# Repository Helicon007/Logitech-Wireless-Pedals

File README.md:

# Logitech G27 Wireless Pedals per ESP-NOW
Ich fahre nur gelegentlich ein paar Runden GT7 und hab dazu noch ein altes Logitech G27 Lenkrad mit Pedalen. Ich musste bereits den optischen Encoder reparieren und war vertraut damit das Lenkrad zu zerlegen. Um das G27 an einer PS5 lauffähig zu bekommen ist ein Adapter nötig, ich nutze den [Ras1ution 2](https://www.brookaccessory.com/products/ras1ution2/index.html) und bin soweit zufrieden, allerdings ist der mittlerweile so teuer dass man auch über ein neues kompatibles Lenkrad nachdenken könnte. 
Da ich mein Setup regelmäßig am Schreibtisch auf- und abbaue habe ich das optimiert. Lenkrad und Schalthebel sind auf einem laminierten Brett geschraubt und die Pedale haben Schienen mit denen ich den Abstand zum Bürostuhl fixieren kann. Das hat aber leider zu Folge dass die Leitungen am Lenkrad fest verbunden sind und beim aufräumen das Kabel zu den Pedalen sehr stört. Das Brett mit Lenkrad und Schalthebel ist quasi über das dünne Kabel mit den Pedalen fest verbunden. Warum also das ganze nicht schnurlos gestalten, die Elektronik hierfür habe ich daheim und ich war eh auf der Suche nach einem neuen Projekt? 
Das ist ein Blog oder Erfahrungsbericht, keine Anleitung. Grundkenntnisse in Elektronik und ESP sind vorausgesetzt. Gerne beantworte ich Fragen aber ich erhebe hier keinen Anspruch auf ein Projekt was problemlos nachgebaut werden kann.

Die Kernelemente sind zwei ESP8622 Boards in Form eines ESP-01 und eines Wemos Klons. Stromversorgung beim Empfänger sollte im Lenkrad zu finden sein, für die Pedale brauchen wir eine Akku-Schaltung mit Ladeelektronik die lange genug durchhält. Eine 18650 Lithium Zelle ist üppig genug und sollte mit 2000mAh circa 11-12h durchhalten. Der Sender benötigt circa 120-150mA, aber zur Wahrheit gehört auch dass wir nicht die gesamte Kappazität der Batterie nutzen können weil unter 3V der ESP dann irgendwann aussteigt. Der Spannungsregler hat entsprechend auch einen Spannungsabfall von 0.1-0.2V. Ich habe mich an fertigen Breakout Boards bedient die ich dann auf einer Lochrasterplatine mit Kupferlackdrähten verbunden habe. Natürlich wäre das alles auf einer schicken Platine schöner aber ich hatte nicht geplant hiermit in die Serienfertigung zu. gehen, das Projekt ist für mich und ich Teile nur meine Erfahrungen falls jemand etwas ähnliches vor hat. 
Die Stücklliste der fertigen Boards:
* ESP-01 + Programmieradapter
* Spannungsregler 3.3V
* Ladeschaltung Li-Ion Akku
* USB-PD Board (optional)
* ADS1115 4-Kanal AD-Wandler mit I2C Bus
* Wemos Pro mini
* Levelshifter 3.3V <—> 5V
* I2C Display (optional)
* Lochrasterplatine
* Kupferlackdraht
* Steckverbinder (Set mit Crimpzange)
* 18650 Akkuzelle mit Halter
* Ein/Aus-Schalter

# Der Sender
Das USB-C PD-Board habe ich genommen weil damit sicher gestellt ist dass auch ein PD-Netzteil Spannung liefert und auch der maximale Ladestrom von 1A damit erreicht werden kann. Ohne dieses funktioniert die Ladeschaltung natürlich auch. Ich hatte aber nur Boards mit Micro-USB Buchse und ein PD-Netzteil würde auch keine Spannung liefern. Ein  USB-A Kabel auf Micro-USB würde funktionieren aber das wollte ich nicht. Ich bin froh wenn irgendwann alle meine Geräte nur noch USB-C benutzen. Deshalb der Aufwand mit dem PD-Breakout Board um mit den 5V dann direkt in das Ladeboard zu gehen. Ich habe hier eins mit Schutzschaltung genommen das vor Unterspannung und Kurzschlussstrom schützt.  Der Ausgang des Boards wird mit dem Spannungswandler verbunden an dem dann der ESP-01 und der ADS1115 angeschlossen wird. Der ESP-01 hat keinen AD Wandler und wir würden ja auch mindestens 3 benötigen, das bietet auch kein Wemos. Weiter ist der on-Board AD Wandler sehr ungenau und von der Versorgungsspannung abhängig. Das AD1115 Board liefert uns hingegen 4 AD-Wander mit eigener Referenzspannung, mit 16 Bit Auflösung und hoher Samplingrate von maximal 860 sps (bei 4 Kanälen entsprechend 860/4). Da bleibt auch noch ein Kanal frei um die Akkuspannung zu überwachen, das ist optional. Genauso wie das OLED Display am Empfänger kann man das auch einfach weglassen. 

Unter dem ADS1115 befindet sich ein einfach Spannungteiler für die Batteriespannung. Die gemessene Spannung darf nicht über den 3,3V VDD liegen und der Akku kann ja bis zu 4,2V haben. Deshalb kommt hier eine Reihenschaltung von 220kOhm und 100kOhm als Teiler.

Ubat —|100k|— A0 — |220k| — GND

Den ADS1115 habe ich ohne Stecksockel auf der Platine verlötet damit ich die Boards stapeln kann und die Fläche klein bleibt. 

Die Pedale bestehen aus je einem 10kOhm Poti. Vom Lenkrad kommen 5V und GND und entsprechend wird an jedem Pedal die Signalspannung abgegriffen. Das ganze funktioniert natürlich auch mit 3,3V da wir ja nur die Position benötigen von 0-100% und einen Rohwert des AD Wandlers verschicken. Auf der Empfängerseite versuchen wir dann wieder so gut wie möglich 0-5V daraus zu machen. 
Den Ein-/Ausschalter habe ich direkt mit der Batteriemasse verbunden. Nicht ganz optimal weil dadurch auch nur im eingeschalteten Zustand der Akku geladen werden kann. Besser wäre es gewesen den Schalter in die Verbindung zur Hauptplatine zu bauen. Andererseits ist das dank Power Delivery Schaltung auch kein Problem zu den 1A Ladestrom auch die 150mA für die Schaltung zu bekommen. Deshalb habe ich es letztlich so gelassen. 
Die vorhandenen Kabel zum Lenkrad habe ich weitergenutzt. Den langen Teil abgeschnitten und einen Stecker für die Hauptplatine angeschlossen. Das war es dann auch auf Senderseite. Natürlich muss auf dem ESP-01 die Sendersoftware auch installiert werden. Wie das funktioniert setze ich voraus, hierfür gibt es aber auch genügend Anleitungen im Netz weshalb ich darauf nicht eingehe. Nur die MAC Adresse des Empfängers ist hart im Programmcode festgelegt und muss entsprechend angepasst werden. Man könnte natürlich auch Broadcast an alle ESP senden aber die Reichweite ist doch recht hoch und ich hab mich für die 1:1 Verbindung entschieden. 

Für die Lade-LEDs habe ich noch zwei 1,5mm Löcher ins Gehäuse gebohrt und anschliesend die Platine danach ausgerichtet und mit Heißkleber fixiert. 
Auch die Kabel sind mit Heißkleber fixiert und einige Stege aus dem Gehäusedeckel eingeschnitten um zu verhindern dass Kabel gequetscht werden. Beim Verschrauben kann man sonst leicht einige Kabel noch beschädigen. 

# Der Empfänger
Ein Wemos Klon gepaart mit einem Level Shifter schien mir hier die einfachste Wahl. Ganz so einfach war es dann aber doch leider nicht. Da ich davon augegangen bin dass der Prozessor im Lenkrad ein glattes Analogsignal sehen möchte und nicht die PWM Ausgänge eines ESP musste die Spannung nachträglich geglättet werden. Die bekannten Levelshifter sind aber sehr hochohmig (10kOhm) was ein RC Tiefpass einfach zu träge gemacht hat. Ich erreichte so aus dem PWM Signal mit 3,3V leider keine 5V. Tatsächlich gehen die 0-100% der Pedale in einer Spannung von 0,6V-4,6V aus, das hab ich im originalzustand vorher gemesssen. Aber auch von den 4,6V war ich noch weit weg. Ein funktionierender Tiefpass würde aus einem 1kOhm Widerstand in Reihe und 10µF Kapazität nach Masse bestehen. So ein Level Shifter hat aber von HV zum Ausgang einen 10kOhm Widerstand. 

Um ausreichend Ladestrom für den 10µF Kondensator am 5V Ausgang zu erhalten habe ich parallel zu R4 im Schaltbild einen 1000 Ohm Widerstand gelötet. Das kann man auf der Lochrasterplatine machen zwischen 5V und dem Ausgang. Somit fällt R4 knapp unter 1000 Ohm. Der Entladestrom des Elkos wäre aber viel zu hoch für den I/O des Wemos weshalb unbedingt zwischen dem Ausgang und dem Elko noch mal 1kOhm in Reihe geschaltet sein muss. Das begrenzt den Strom auf 5mA was für den Wemos kein Problem ist. Das RC Glied besteht dann am Ende aus 2kOhm und 10µF. Immer noch gut genug die Spannung zu glätten und ein Maximum von circa 4,6V zu erreichen. Damit ist dann auch der Prozessor im Lenkrad zufrieden.

Ich habe leider versäumt ein schönes Foto vom Levelshifter zu machen aber ich habe ihn direkt auf der Platine unter dem Wemos verlötet. Daneben sind die SMD Elkos zu erkennen und die Widerstände habe ich auf der Rückseite verlötet.

Das OLED ist komplett optional und hier nur gesteckt. Später im Lenkrad habe ich das über eine 4-adrige Leitung verbunden. Es zeigt mir später die Spannung der Senderbatterie an und den Zustand des Gas- und Bremspedals, allerdings nur mit Latenz. Das PWM Signal reagiert unmittelbar auf die Pedale aber das Display schreibe ich im Code nur einmal pro Sekunde. Ohne zu überprüfen dachte ich mir die Rechenzeit des ESP ist besser aufgehoben möglichst schnell das PWM anzupassen und weniger das Display. Die einzige sinnvolle Information ist die Batteriespannung und die muss nicht unmittelbar angezeigt werden. 

Der Anschluss der Pedale ist auf dem Mainboard unten links. Leider sind die Kabelfarben nicht identisch mit den Farben der Leitung zu den Pedalen. Gut wenn man sich vorher die Belegung vom Sub-D Stecker aufgeschrieben hat.

* 1 GND
* 2 Gas
* 3 Bremse
* 4 Kupplung
* 6 Enable Pin active high
* 9 +5V

Leider ist die Spannungsversorgung nicht ohne Schutzwiderstand und wir können die Schaltung nicht mit dem 5V Anschluss links betreiben. Die Spannung fällt augenblicklich auf 1V, ein Strom von 150mA kann hier nicht direkt abgegriffen werden. Deshalb habe ich die 5V direkt am USB Anschluss des Lenkrads abgegriffen, der grüne Pin am rechten Stecker. Hierfür brückte ich direkt auf der Rückseite mit einem Kupferlackdraht die Verbindung. Da auf den zwei Pins ohne Last dasselbe Potential lag machte ich mir über die Hauptplatine keine Sorgen. Vermutlich ist hier nur ein Schutzwiderstand eingebracht der die Platine vor einem Kurzschluss am Ausgang absichert der ja ohnehin nicht mehr benötigt wird. 

Der braune Pin ist wohl eine Art Enabler. Die Pedale werden erst erkannt wenn auf diesem Pin High anliegt, also mit 5V verbinden. USB Plus ist grün und das Kabel ist braun?! Verlasst Euch nicht auf irgendeine Farbenregel, messt selbst nach. Auf dem Sub-D Kabel ist Pin 9 und 6 verbunden. 
Jetzt noch einen Platz für die Platine und optional das Display finden und wir sind fertig.

Wie gesagt das Display ist komplett optional aber anders kann ich die Spannung des Akkus natürlich nicht anzeigen. Im Zweifel wäre halt irgendwann die Batterie leer, wer kennt es nicht von seiner Maus. Immer wenn es darauf ankommt müssen die Akkus gewechselt werden ;o) 
Weiter sollte man je nach Spiel immer überprüfen ob die Pedale auch wirklich 100% erreichen. Für GT7 kam ich manchmal nur auf 99,5% was man nicht haben möchte. Also vorher die Kalibrierung prüfen, es macht einen Unterschied. Die Reaktionsgeschwindigkeit ist hoch genug, man bekommt auf der Konsole in der Regel ja auch nicht mehr als 60fps und damit kann der ESP locker mithalten. Um ein wenig Strom zu sparen hab ich die Samplingrate auf 120/s begrenzt. Das spart circa 20% Strom und reicht aus meiner Sicht vollkommen aus. Man kann den Code natürlich auch anpassen um das Maximum heraus zu holen aber mehr als 215 kann der ADS1115 ohnehin nicht. 860 Samples geteilt durch 4 Kanäle.

Natürlich wäre auch eine fertige Platine schön gewesen aber wie es halt mal so ist - ich habe nur ein Lenkrad und der Prototyp funktioniert. Jeder Bastler weiß - nichts hält so lange wie ein Prototyp, sorry. Sollte es mich aber doch mal eines Tages reizen werde ich das nachliefern. Wartet aber bitte nicht darauf, da muss es mir schon sehr langweilig werden. Es war halt leicht mit dem Material was ohnehin bei mir rum fliegt etwas zu machen und die Breakout Boards vom China-Mann sind einfach unschlagbar günstig. 

P.S.: 11.08.2025 und mir war es langweilig. Ich habe ein KiCAD Projekt entworfen mit einem PCB Design. Allerdings kommen hier nur der ESP-01 und der Wemos als fertiges Modul zum Einsatz, alles weitere ist in SMD ausgelegt. 1206er Bauteile mit hoffentlich lötfreundlichen Pads. 

So sieht es vor dem Verlöten auf der Hot Plate (G3061) aus.

Und hier der fertige Empfänger. Für den Sender muss ich leider noch mal auf Ferrite Beads warten weil in der ersten Lieferung nur einfache Widerstände enthalten waren. Also noch mal neu geordert bei einem anderen Lieferanten. 

Sich das verlöten unter dem Mikroskop anzuschauen ist seltsam befriedigend und will ich Euch nicht vorenthalten :) 

### [Soldering process on YouTube](https://youtu.be/-KurLvUTaSc)

P.P.S: 23.08.2025: Der AMS1117 Spannungsregler entpuppt sich als Designfehler. Der Spannungsabfall >1V macht ihn für Eingangsspannungen von >5V geeignet, nicht aber für einen Lithium Akku. Geeignete LDO Regler wie der HT7333 haben den Vin und Vout leider vertauscht, ich habe kein Pinkompatibles SOP-233 Bauteil gefunden weshalb ich die Senderplatine noch mal verändern muss. Die Bilder oben zeigen noch die Version 0.1 mit dem AMS1117.

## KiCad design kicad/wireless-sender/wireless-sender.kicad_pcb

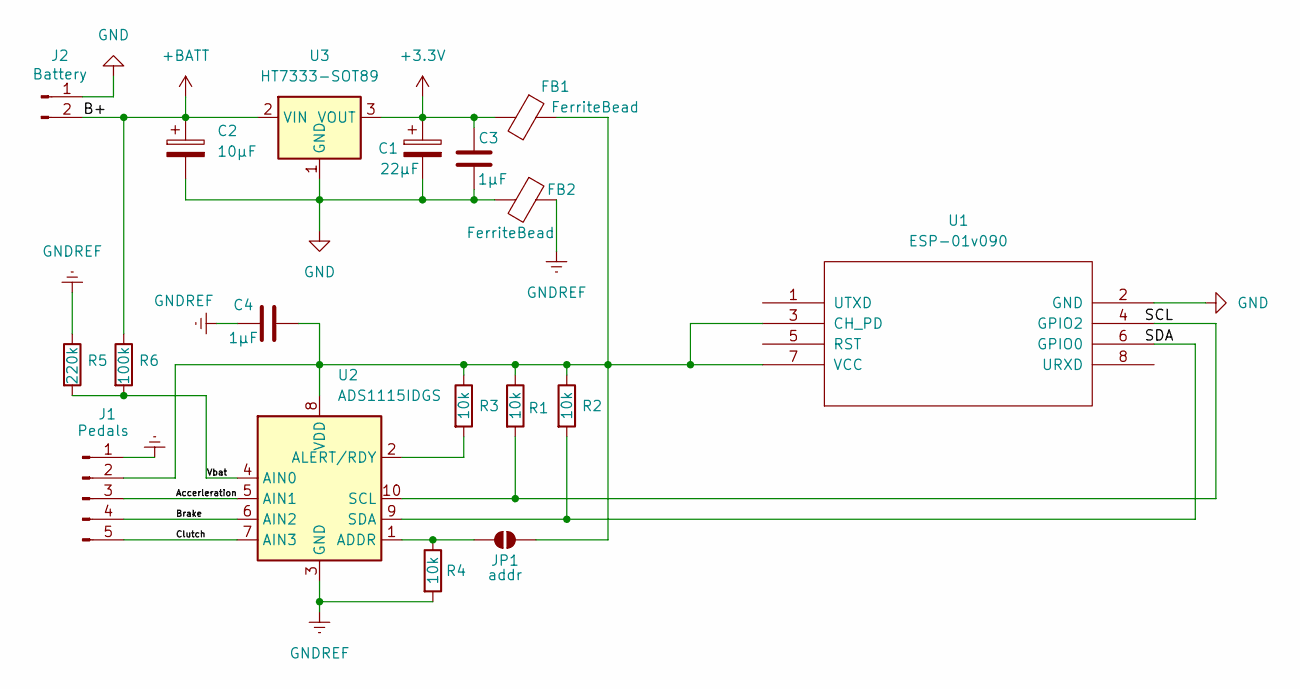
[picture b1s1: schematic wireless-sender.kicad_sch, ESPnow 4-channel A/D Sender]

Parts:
C1: 22µF; C_1206_3216Metric_Pad1.33x1.80mm_HandSolder
C2: 10µF; C_1206_3216Metric_Pad1.33x1.80mm_HandSolder
C3, C4: 1µF; C_1206_3216Metric_Pad1.33x1.80mm_HandSolder
FB1, FB2: FerriteBead; L_1206_3216Metric_Pad1.22x1.90mm_HandSolder
J1: Pedals; PinHeader_1x05_P2.54mm_Vertical
J2: Battery; PinHeader_1x02_P2.54mm_Vertical
JP1: addr; SolderJumper-2_P1.3mm_Open_TrianglePad1.0x1.5mm
R1, R2, R3, R4: 10k; R_1206_3216Metric_Pad1.30x1.75mm_HandSolder
R5: 220k; R_1206_3216Metric_Pad1.30x1.75mm_HandSolder
R6: 100k; R_1206_3216Metric_Pad1.30x1.75mm_HandSolder
U1: ESP-01v090; ESP-01
U2: ADS1115IDGS; MSOP-10_3x3mm_P0.5mm
U3: HT7333-SOT89; SOT-89-3

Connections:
+3.3V: C1.1, C3.1, FB1.2, U3.3 (VOUT)
+BATT: C2.1, J2.2, R6.1, U3.2 (VIN)
/Accerleration: J1.3, U2.5 (AIN1)
/Brake: J1.4, U2.6 (AIN2)
/Clutch: J1.5, U2.7 (AIN3)
/Vbat: R5.2, R6.2, U2.4 (AIN0)
GND: C1.2, C2.2, C3.2, FB2.2, J2.1, U1.2 (GND), U3.1 (GND)
GNDREF: C4.1, FB2.1, J1.1, R4.2, R5.1, U2.3 (GND)
unnamed: C4.2, FB1.1, J1.2, JP1.1 (A), R1.1, R2.1, R3.1, U1.3 (CH_PD), U1.7 (VCC), U2.8 (VDD)
unnamed: JP1.2 (B), R4.1, U2.1 (ADDR)
unnamed: R2.2, U1.6 (GPIO0), U2.9 (SDA)
unnamed: R1.2, U1.4 (GPIO2), U2.10 (SCL)
unnamed: R3.2, U2.2 (ALERT/RDY)

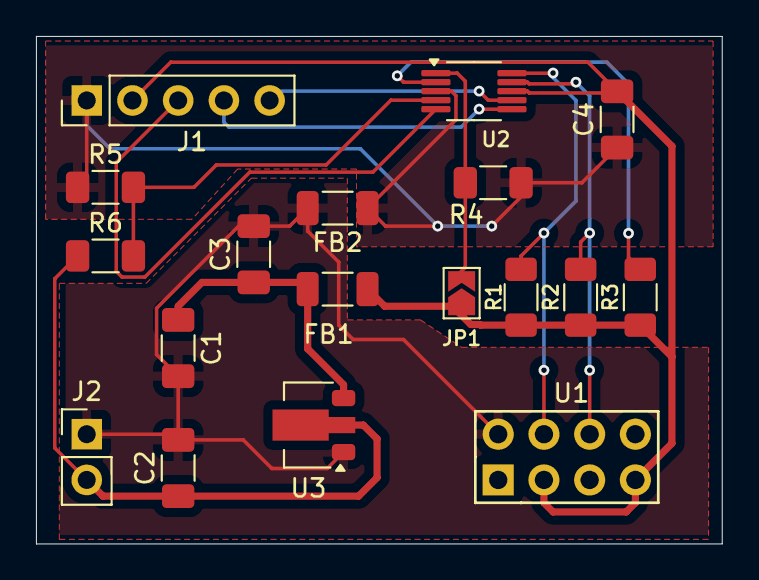
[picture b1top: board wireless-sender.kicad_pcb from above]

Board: 2 copper layers, 38.1 x 28.2 mm, 18 parts (0 on the bottom side), 13 nets.

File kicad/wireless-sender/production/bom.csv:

Designator,Footprint,Quantity,Value,LCSC Part #
ADS1115,MSOP-10_3x3mm_P0.5mm,1,ADS1115IDGS,
AMS1117,SOT-223-3_TabPin2,1,AMS1117-3.3,
C1,1206,1,22µF,
C2,1206,1,10µF,
"C3, C4",1206,2,1µF,
ESP-01,ESP-01,1,ESP-01v090,
"FB1, FB2",1206,2,FerriteBead,
J1,PinHeader_1x05_P2.54mm_Vertical,1,Pedals,
J2,PinHeader_1x02_P2.54mm_Vertical,1,Battery,
"R1, R2, R3, R4",1206,4,10k,
R5,1206,1,220k,
R6,1206,1,100k,

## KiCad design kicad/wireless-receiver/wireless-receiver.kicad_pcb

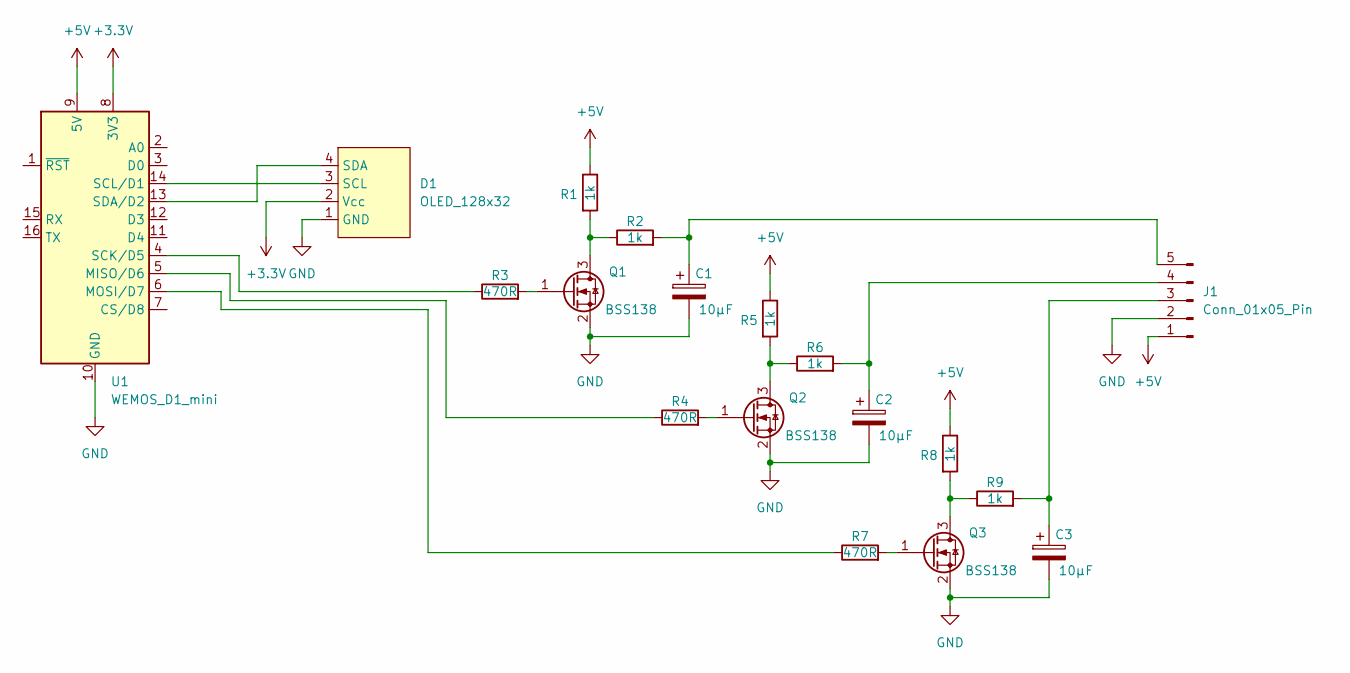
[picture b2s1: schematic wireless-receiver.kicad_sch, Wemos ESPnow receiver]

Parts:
C1, C2, C3: 10µF; C_1206_3216Metric_Pad1.33x1.80mm_HandSolder
D1: OLED_128x32; PinSocket_1x04_P2.54mm_Vertical
J1: Conn_01x05_Pin; PinSocket_1x05_P2.54mm_Vertical
Q1, Q2, Q3: BSS138; SOT-23
R1, R2, R5, R6, R8, R9: 1k; R_1206_3216Metric_Pad1.30x1.75mm_HandSolder
R3, R4, R7: 470R; R_1206_3216Metric_Pad1.30x1.75mm_HandSolder
U1: WEMOS_D1_mini; WEMOS_D1_mini_light

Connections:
+3.3V: D1.2 (Vcc), U1.8 (3V3)
+5V: J1.1, R1.1, R5.1, R8.1, U1.9 (5V)
GND: C1.2, C2.2, C3.2, D1.1 (GND), J1.2, Q1.2 (S), Q2.2 (S), Q3.2 (S), U1.10 (GND)
unnamed: D1.3 (SCL), U1.14 (SCL/D1)
unnamed: D1.4 (SDA), U1.13 (SDA/D2)
unnamed: C3.1, J1.3, R9.2
unnamed: C2.1, J1.4, R6.2
unnamed: C1.1, J1.5, R2.2
unnamed: Q1.3 (D), R1.2, R2.1
unnamed: Q1.1 (G), R3.2
unnamed: Q2.3 (D), R5.2, R6.1
unnamed: Q2.1 (G), R4.2
unnamed: Q3.3 (D), R8.2, R9.1
unnamed: Q3.1 (G), R7.2
unnamed: R4.1, U1.5 (MISO/D6)
unnamed: R7.1, U1.6 (MOSI/D7)
unnamed: R3.1, U1.4 (SCK/D5)

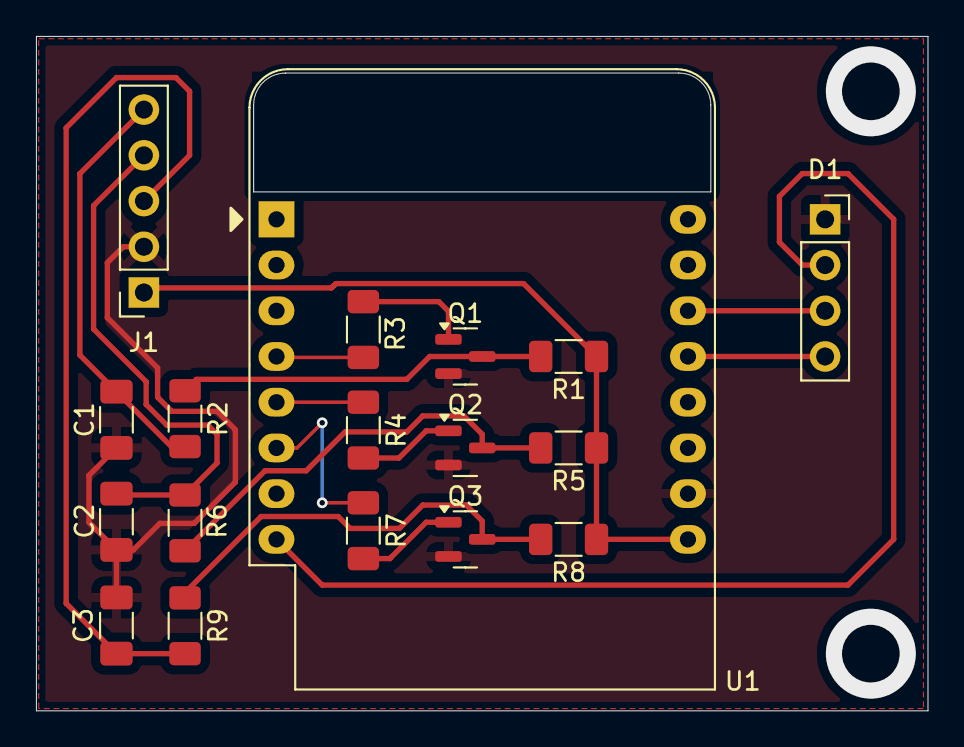
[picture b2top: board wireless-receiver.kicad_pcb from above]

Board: 2 copper layers, 49.5 x 37.5 mm, 18 parts (0 on the bottom side), 17 nets.

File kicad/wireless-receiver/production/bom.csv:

Designator,Footprint,Quantity,Value,LCSC Part #
"C1, C2, C3",1206,3,10µF,
D1,PinSocket_1x04_P2.54mm_Vertical,1,OLED_128x32,
J1,PinSocket_1x05_P2.54mm_Vertical,1,Conn_01x05_Pin,
"Q1, Q2, Q3",SOT-23,3,BSS138,
"R1, R2, R5, R6, R8, R9",1206,6,1k,
"R3, R4, R7",1206,3,470R,
U1,WEMOS_D1_mini_light,1,WEMOS_D1_mini,

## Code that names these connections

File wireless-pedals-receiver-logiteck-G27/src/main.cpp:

#include <Arduino.h>
#include <ESP8266WiFi.h>
#include <ESPNowW.h>
#include <stdio.h>
#include <U8g2lib.h>

typedef struct struct_message {
  int16_t a0;
  int16_t a1;
  int16_t a2;
  int16_t a3;
} struct_message;

struct_message incomingData;

// ADS1115 Settings
#define ADS_RANGE 4.096  // GAIN_ONE
#define ADS_MAX_VALUE 32767.0  // 15bit
#define INPUT_VOLTAGE_MAX 3.3

// Display graphics
static const uint8_t image_battery_33_bits[] = {0x00,0x00,0x00,0xf0,0xff,0x7f,0x08,0x00,0x80,0x08,0x00,0xb6,0x0e,0x00,0xb6,0x01,0x00,0xb6,0x01,0x00,0xb6,0x01,0x00,0xb6,0x01,0x00,0xb6,0x01,0x00,0xb6,0x0e,0x00,0xb6,0x08,0x00,0xb6,0x08,0x00,0x80,0xf0,0xff,0x7f,0x00,0x00,0x00,0x00,0x00,0x00};
static const uint8_t image_battery_67_bits[] = {0x00,0x00,0x00,0xf0,0xff,0x7f,0x08,0x00,0x80,0x08,0xd8,0xb6,0x0e,0xd8,0xb6,0x01,0xd8,0xb6,0x01,0xd8,0xb6,0x01,0xd8,0xb6,0x01,0xd8,0xb6,0x01,0xd8,0xb6,0x0e,0xd8,0xb6,0x08,0xd8,0xb6,0x08,0x00,0x80,0xf0,0xff,0x7f,0x00,0x00,0x00,0x00,0x00,0x00};
static const uint8_t image_battery_83_bits[] = {0x00,0x00,0x00,0xf0,0xff,0x7f,0x08,0x00,0x80,0x08,0xdb,0xb6,0x0e,0xdb,0xb6,0x01,0xdb,0xb6,0x01,0xdb,0xb6,0x01,0xdb,0xb6,0x01,0xdb,0xb6,0x01,0xdb,0xb6,0x0e,0xdb,0xb6,0x08,0xdb,0xb6,0x08,0x00,0x80,0xf0,0xff,0x7f,0x00,0x00,0x00,0x00,0x00,0x00};
static const uint8_t image_battery_empty_bits[] = {0x00,0x00,0x00,0xf0,0xff,0x7f,0x08,0x00,0x80,0x08,0x00,0x80,0x0e,0x00,0x80,0x01,0x00,0x80,0x01,0x00,0x80,0x01,0x00,0x80,0x01,0x00,0x80,0x01,0x00,0x80,0x0e,0x00,0x80,0x08,0x00,0x80,0x08,0x00,0x80,0xf0,0xff,0x7f,0x00,0x00,0x00,0x00,0x00,0x00};
static const uint8_t image_battery_full_bits[] = {0x00,0x00,0x00,0xf0,0xff,0x7f,0x08,0x00,0x80,0x68,0xdb,0xb6,0x6e,0xdb,0xb6,0x61,0xdb,0xb6,0x61,0xdb,0xb6,0x61,0xdb,0xb6,0x61,0xdb,0xb6,0x61,0xdb,0xb6,0x6e,0xdb,0xb6,0x68,0xdb,0xb6,0x08,0x00,0x80,0xf0,0xff,0x7f,0x00,0x00,0x00,0x00,0x00,0x00};
static const uint8_t image_radio_bits[] = {0x00,0x00,0x00,0x00,0x00,0x00,0x04,0x40,0x00,0x02,0x80,0x00,0x12,0x90,0x00,0x09,0x21,0x01,0xa5,0x4b,0x01,0x95,0x52,0x01,0xa5,0x4b,0x01,0x09,0x21,0x01,0x12,0x90,0x00,0x02,0x80,0x00,0x04,0x40,0x00,0x00,0x00,0x00,0x00,0x00,0x00,0x00,0x00,0x00};

// OLED
// U8G2_SH1106_128X32_VISIONOX_1_HW_I2C u8g2(U8G2_R0, /* reset=*/ U8X8_PIN_NONE);
//U8G2_SSD1306_128X32_UNIVISION_1_SW_I2C u8g2(U8G2_R0, /* clock=*/ 21, /* data=*/ 20, /* reset=*/ U8X8_PIN_NONE);   // Adafruit Feather M0 Basic Proto + FeatherWing OLED
//U8G2_SSD1306_128X32_UNIVISION_1_SW_I2C u8g2(U8G2_R0, /* clock=*/ SCL, /* data=*/ SDA, /* reset=*/ U8X8_PIN_NONE);   // Adafruit Feather ESP8266/32u4 Boards + FeatherWing OLED
U8G2_SSD1306_128X32_UNIVISION_1_HW_I2C u8g2(U8G2_R0, /* reset=*/ U8X8_PIN_NONE);   // Adafruit ESP8266/32u4/ARM Boards + FeatherWing OLED
//U8G2_SSD1306_128X32_UNIVISION_1_HW_I2C u8g2(U8G2_R0, /* reset=*/ U8X8_PIN_NONE, /* clock=*/ SCL, /* data=*/ SDA);   // pin remapping with ESP8266 HW I2C
// U8G2_SSD1306_128X32_WINSTAR_1_HW_I2C u8g2(U8G2_R0, /* reset=*/ U8X8_PIN_NONE, /* clock=*/ SCL, /* data=*/ SDA);   // pin remapping with ESP8266 HW I2C


// PWM Pins (z. B. D1, D2, D3)
const int pwmPin1 = D5;  // accerleration
const int pwmPin2 = D6;  // brake
const int pwmPin3 = D7;  // clutch

char u_bat[5];
unsigned long previousTime = 0;
unsigned long actualTime = millis();


void OnDataRecv(uint8_t *mac, uint8_t *incomingDataRaw, uint8_t len);

void updateOLED(float voltage, int acc, int brake);

void setup() {
  Serial.begin(57600);
  WiFi.mode(WIFI_STA);
  WiFi.disconnect();

  pinMode(pwmPin1, OUTPUT);
  pinMode(pwmPin2, OUTPUT);
  pinMode(pwmPin3, OUTPUT);

  analogWriteRange(1023);  // 10-bit PWM

  if (esp_now_init() != 0) {
    Serial.println("Fehler beim Initialisieren von ESP-NOW");
    return;
  }

  // OLED Init
  delay(250); // wait for the OLED to power up
  u8g2.begin();

  esp_now_set_self_role(ESP_NOW_ROLE_SLAVE);
  esp_now_register_recv_cb(OnDataRecv);

  u8g2.firstPage();
  do {
    u8g2.setFont(u8g2_font_6x10_tr);
    u8g2.setDrawColor(1);
    // no data so far
    u8g2.drawStr(12,13,"Device ready");
    u8g2.drawStr(12,27,"no data received");
    } while ( u8g2.nextPage() );
}

void OnDataRecv(uint8_t *mac, uint8_t *incomingDataRaw, uint8_t len) {
  memcpy(&incomingData, incomingDataRaw, sizeof(incomingData));

  // Umrechnung: Rohwert → Spannung → PWM (0–1023)
  float v0 = (incomingData.a0 * ADS_RANGE) / ADS_MAX_VALUE;
  float v1 = (incomingData.a1 * ADS_RANGE) / ADS_MAX_VALUE;
  float v2 = (incomingData.a2 * ADS_RANGE) / ADS_MAX_VALUE;
  float v3 = (incomingData.a3 * ADS_RANGE) / ADS_MAX_VALUE;

  // Begrenzen auf 0–3.3V
  v1 = constrain(v1, 0.0, INPUT_VOLTAGE_MAX);
  v2 = constrain(v2, 0.0, INPUT_VOLTAGE_MAX);
  v3 = constrain(v3, 0.0, INPUT_VOLTAGE_MAX);

  int pwm1 = (v1 / INPUT_VOLTAGE_MAX) * 1023;
  int pwm2 = (v2 / INPUT_VOLTAGE_MAX) * 1023;
  int pwm3 = (v3 / INPUT_VOLTAGE_MAX) * 1023;

  analogWrite(pwmPin1, pwm1);
  analogWrite(pwmPin2, pwm2);
  analogWrite(pwmPin3, pwm3);

  v0 = (v0 * 320) / 220;         // voltage divider  GND----220k--*--100k----V_bat 

  /* only for debug  
  dtostrf(v0, 4, 2, u_bat);
  Serial.printf("PWM1=%d raw=%d | PWM2=%d raw=%d | PWM3=%d raw=%d | Vbat=%sV raw=%d \n", pwm1, incomingData.a1, pwm2, incomingData.a2, pwm3, incomingData.a3, u_bat, incomingData.a0);
 */

  // OLED update once per second
  actualTime = millis();
  if (actualTime - previousTime >= 1000) {
    previousTime = actualTime;
    updateOLED(v0, pwm1, pwm2);
  }
  
}

void updateOLED(float voltage, int acc, int brake) {
  dtostrf(voltage, 4, 2, u_bat);
  u8g2.firstPage();
  do {
    u8g2.setFont(u8g2_font_6x10_tr);
    u8g2.setDrawColor(1);
    // about the battery
    u8g2.drawStr(12,13,u_bat);
    u8g2.drawStr(36,13,"V");
    if (voltage >= 3.9) {
      u8g2.drawXBM(56, 2, 24, 16, image_battery_full_bits);
    } else if (voltage >= 3.7) {
      u8g2.drawXBM(56, 2, 24, 16, image_battery_83_bits);
    } else if (voltage >= 3.5) {
      u8g2.drawXBM(56, 2, 24, 16, image_battery_67_bits);     
    } else if (voltage >= 3.2) {
      u8g2.drawXBM(56, 2, 24, 16, image_battery_33_bits);     
    }  else {
      u8g2.drawXBM(56, 2, 24, 16, image_battery_empty_bits);     
    }

    u8g2.drawXBM(99, 2, 17, 16, image_radio_bits);  // makes actually no sense because only with radio the display is updated, but it looks nice ;o) 

    // about the acc and brake pedal
    acc = constrain(acc, 150, 940);
    brake = constrain(brake, 150, 940);
    int a = map(acc, 940, 150, 0, 100);
    int b = map(brake, 940, 150, 0, 100);
    u8g2.drawBox(14, 20, a, 4);
    u8g2.drawBox(14, 28, b, 4);

    
  } while ( u8g2.nextPage() );
}

void loop() {
  // do nothing
}

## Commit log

2025-05-30 First collection
    This is the first Github upload of this project. Detailed Readme's are following.
2025-06-15 README update
    Readme Blog
2025-06-15 Update remark
2025-06-24 Update README.md
    Rechtschreibung und andere Fehler korrigiert.
2025-08-09 Add KiCAD schematics
    I made schematics and a PCB design with KiCAD
2025-08-09 moved some files
2025-08-14 Add PCB pictures
    Added some pictures for documentation.
2025-08-23 PCB Update
    Replaced AMS1117 with HT7333.
